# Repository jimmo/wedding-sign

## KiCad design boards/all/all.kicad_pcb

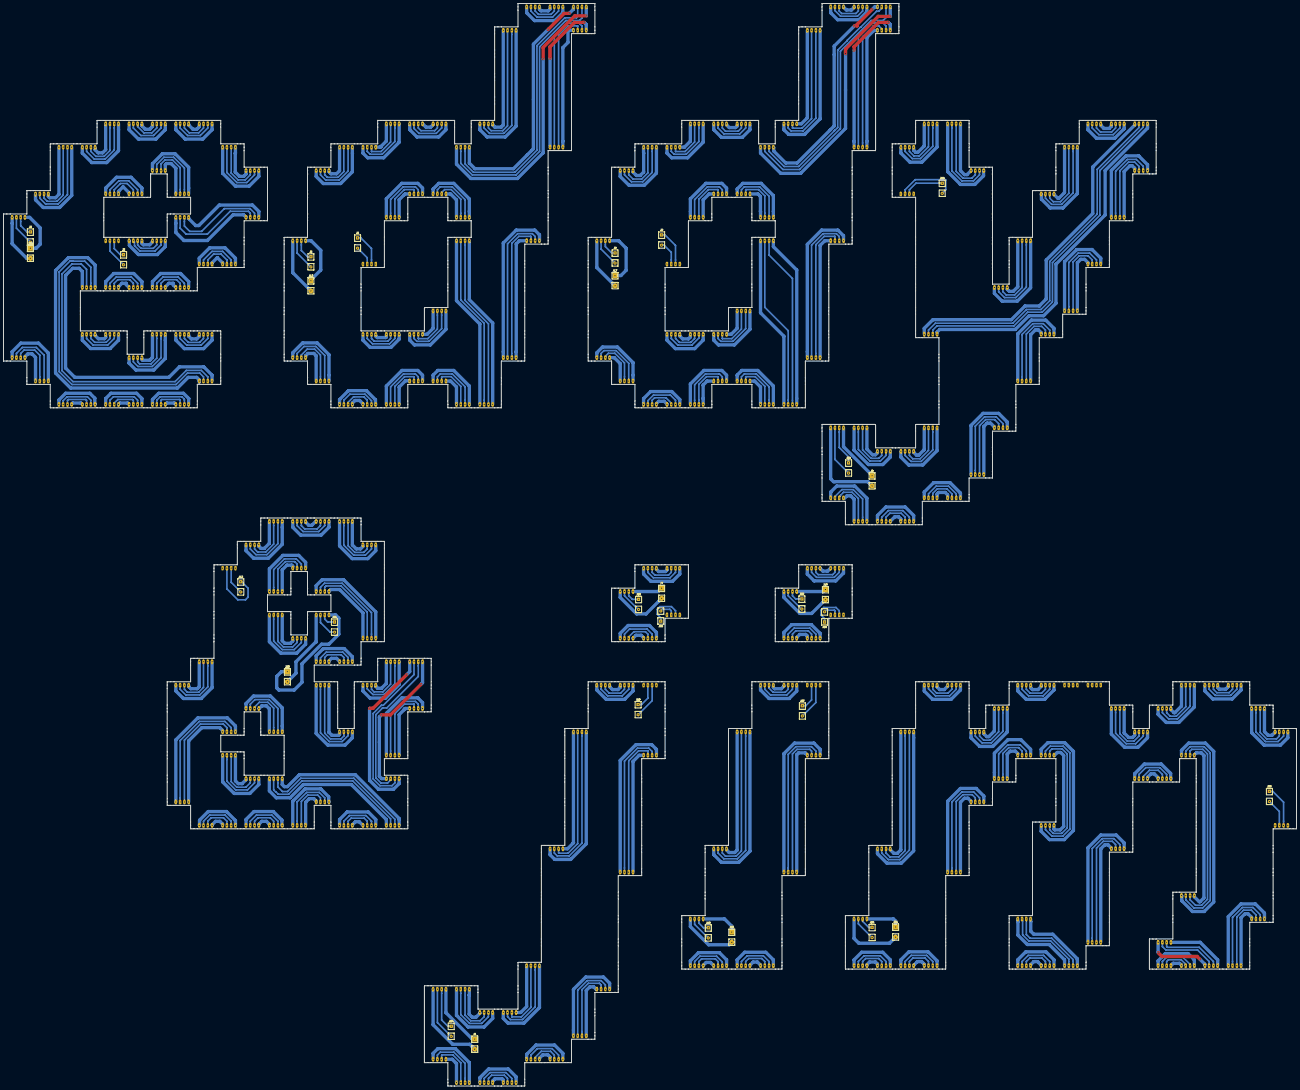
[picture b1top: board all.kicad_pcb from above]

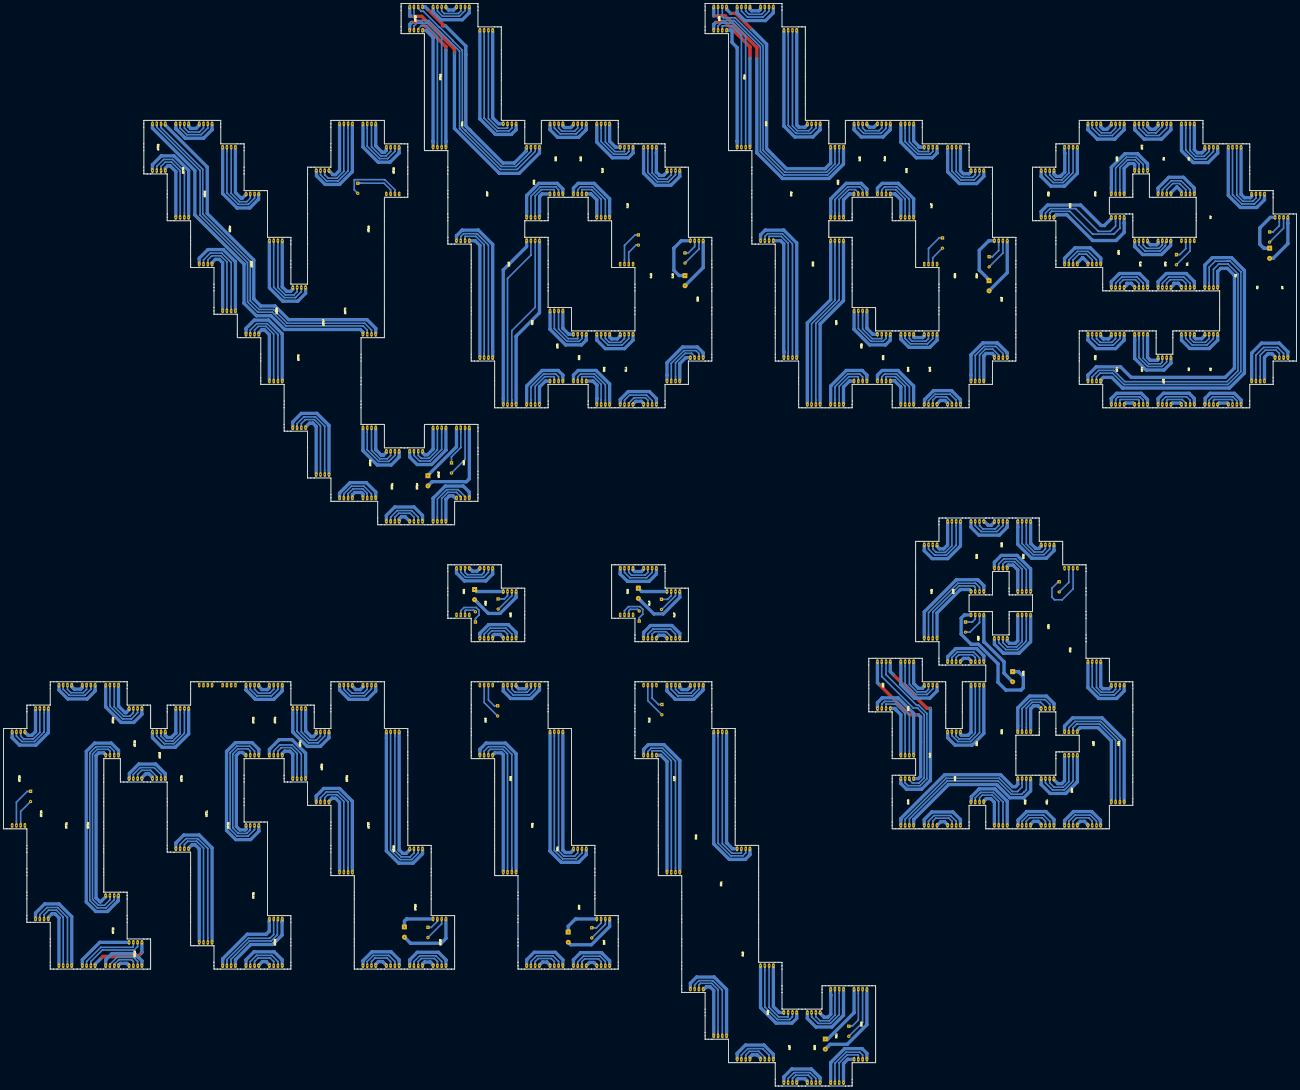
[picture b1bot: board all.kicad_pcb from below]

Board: 2 copper layers, 767.9 x 642.9 mm, 169 parts (139 on the bottom side), 558 nets.

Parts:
J1, J4, J7, J10, J13, J15, J17, J21, J23, J25: CONN_01X02; Power_Connector
J2, J3, J5, J6, J8, J9, J11, J12, J14, J16, J18, J19, J20, J22, J24, J26, J27, J28, J29, J30: CONN_01X02; Sign_Connector
U1, U4, U19, U39, U44, U64, U100, U116, U118, U121, U123, U126, U129: APA102C_x6; APA102C_72m_x6
U2, U33, U72, U93, U113: APA102C_x8; APA102C_72m_x8
U3, U38, U73, U127: APA102C_x11; APA102C_72m_x11
U5, U6, U8, U9, U14, U15, U16, U17, U24, U28, U35, U42, U46, U49, U52, U53, U54, U55, U59, U61, U74, U75, U77, U80, U82, U85, U86, U88, U95, U96, U98, U104, U107, U110, U115, U117, U119, U122, U132, U134, U135: APA102C_x3; APA102C_72m_x3
U7, U10, U11, U12, U13, U20, U25, U27, U30, U32, U36, U48, U50, U51, U71, U78, U81, U83, U92, U99, U102, U106, U120, U130, U131: APA102C_x2; APA102C_72m_x2
U18, U22, U29, U31, U37, U41, U68, U76, U84, U105: APA102C_x5; APA102C_72m_x5
U21, U23, U26, U56, U89, U124: APA102C_x7; APA102C_72m_x7
U34, U65, U70, U109, U138: APA102C_x9; APA102C_72m_x9
U40, U43, U45, U47, U57, U63, U79, U101, U128, U139: APA102C_x4; APA102C_72m_x4
U58, U90, U91, U111, U125, U136, U137: APA102C_x12; APA102C_72m_x12
U60, U94: APA102C_x14; APA102C_72m_x14
U62, U87, U97, U108: APA102C_x10; APA102C_72m_x10
U66, U103, U133: APA102C_x1; APA102C_72m_x1
U67, U69, U114: APA102C_x13; APA102C_72m_x13
U112: APA102C_x16; APA102C_72m_x16

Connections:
+5V: J1.2, J4.2, J7.2, J10.2, J13.2, J15.2, J17.2, J21.2, J23.2, J25.2, U1.4, U31.4, U36.4, U54.4, U68.4, U71.4, U81.4, U92.4, U98.4, U102.4
GND: J1.1, J4.1, J7.1, J10.1, J13.1, J15.1, J17.1, J21.1, J23.1, J25.1, U1.1, U31.1, U36.1, U54.1, U68.1, U71.1, U81.1, U92.1, U98.1, U102.1
unnamed: J2.1, U1.2
unnamed: J2.2, U1.3
unnamed: J3.1, U7.7
unnamed: J3.2, U7.6
unnamed: J5.1, U31.2
unnamed: J5.2, U31.3
unnamed: J6.1, U41.6
unnamed: J6.2, U41.7
unnamed: J8.1, U68.2
unnamed: J8.2, U68.3
unnamed: J9.1, U76.6
unnamed: J9.2, U76.7
unnamed: J11.1, U36.2
unnamed: J11.2, U36.3
unnamed: J12.1, U23.6
unnamed: J12.2, U23.7
unnamed: J14.1, U54.2
unnamed: J14.2, U54.3
unnamed: J16.1, U71.2
unnamed: J16.2, U71.3
unnamed: J18.1, U81.2
unnamed: J18.2, U81.3
unnamed: J19.1, U75.6
unnamed: J19.2, U75.7
unnamed: J20.1, U78.6
unnamed: J20.2, U78.7
unnamed: J22.1, U92.2
unnamed: J22.2, U92.3
unnamed: J24.1, U98.2
unnamed: J24.2, U98.3
unnamed: J26.1, U102.2
unnamed: J26.2, U102.3
unnamed: J27.1, U96.6
unnamed: J27.2, U96.7
unnamed: J28.1, U99.6
unnamed: J28.2, U99.7
unnamed: J29.1, U106.6
unnamed: J29.2, U106.7
unnamed: J30.1, U139.6
unnamed: J30.2, U139.7
unnamed: U1.5, U2.1
unnamed: U1.6, U2.2
unnamed: U1.7, U2.3
unnamed: U1.8, U2.4
unnamed: U2.5, U3.1
unnamed: U2.6, U3.2
unnamed: U2.7, U3.3
unnamed: U2.8, U3.4
unnamed: U3.5, U5.1
unnamed: U3.6, U5.2
unnamed: U3.7, U5.3
unnamed: U3.8, U5.4
unnamed: U4.5, U6.1
unnamed: U4.6, U6.2
unnamed: U4.7, U6.3
unnamed: U4.8, U6.4
unnamed: U5.5, U8.1
unnamed: U5.6, U8.2
unnamed: U5.7, U8.3
unnamed: U5.8, U8.4
unnamed: U6.5, U9.1
unnamed: U6.6, U9.2
unnamed: U6.7, U9.3
unnamed: U6.8, U9.4
unnamed: U10.1, U13.5
unnamed: U10.2, U13.6
unnamed: U10.3, U13.7
unnamed: U10.4, U13.8
unnamed: U7.1, U10.5
unnamed: U7.2, U10.6
unnamed: U7.3, U10.7
unnamed: U7.4, U10.8
unnamed: U8.5, U11.1
unnamed: U8.6, U11.2
unnamed: U8.7, U11.3
unnamed: U8.8, U11.4
unnamed: U11.5, U14.1
unnamed: U11.6, U14.2
unnamed: U11.7, U14.3
unnamed: U11.8, U14.4
unnamed: U9.5, U12.1
unnamed: U9.6, U12.2
unnamed: U9.7, U12.3
unnamed: U9.8, U12.4
unnamed: U12.5, U15.1
unnamed: U12.6, U15.2
unnamed: U12.7, U15.3
unnamed: U12.8, U15.4
unnamed: U13.1, U16.5
unnamed: U13.2, U16.6
unnamed: U13.3, U16.7
unnamed: U13.4, U16.8
unnamed: U14.5, U17.1
unnamed: U14.6, U17.2
unnamed: U14.7, U17.3
unnamed: U14.8, U17.4
unnamed: U15.5, U19.1
unnamed: U15.6, U19.2
unnamed: U15.7, U19.3
unnamed: U15.8, U19.4
unnamed: U16.1, U25.5
unnamed: U16.2, U25.6
unnamed: U16.3, U25.7
unnamed: U16.4, U25.8
unnamed: U17.5, U20.1
unnamed: U17.6, U20.2
unnamed: U17.7, U20.3
unnamed: U17.8, U20.4
unnamed: U18.1, U21.5
unnamed: U18.2, U21.6
unnamed: U18.3, U21.7
unnamed: U18.4, U21.8
unnamed: U18.5, U23.1
unnamed: U18.6, U23.2
unnamed: U18.7, U23.3
unnamed: U18.8, U23.4
unnamed: U19.5, U22.1
unnamed: U19.6, U22.2
unnamed: U19.7, U22.3
unnamed: U19.8, U22.4
unnamed: U4.1, U20.5
unnamed: U4.2, U20.6
unnamed: U4.3, U20.7
unnamed: U4.4, U20.8
unnamed: U21.1, U24.5
unnamed: U21.2, U24.6
unnamed: U21.3, U24.7
unnamed: U21.4, U24.8
unnamed: U22.5, U25.1
unnamed: U22.6, U25.2
unnamed: U22.7, U25.3
unnamed: U22.8, U25.4
unnamed: U24.1, U27.5
unnamed: U24.2, U27.6
unnamed: U24.3, U27.7
unnamed: U24.4, U27.8
unnamed: U26.1, U28.5
unnamed: U26.2, U28.6
unnamed: U26.3, U28.7
unnamed: U26.4, U28.8
unnamed: U26.5, U29.1
unnamed: U26.6, U29.2
unnamed: U26.7, U29.3
unnamed: U26.8, U29.4
unnamed: U27.1, U30.5
unnamed: U27.2, U30.6
unnamed: U27.3, U30.7
unnamed: U27.4, U30.8
unnamed: U28.1, U32.5
unnamed: U28.2, U32.6
unnamed: U28.3, U32.7
unnamed: U28.4, U32.8
unnamed: U29.5, U33.1
unnamed: U29.6, U33.2
unnamed: U29.7, U33.3
unnamed: U29.8, U33.4
unnamed: U30.1, U48.5
unnamed: U30.2, U48.6
unnamed: U30.3, U48.7
unnamed: U30.4, U48.8
unnamed: U31.5, U34.1
unnamed: U31.6, U34.2
unnamed: U31.7, U34.3
unnamed: U31.8, U34.4
unnamed: U32.1, U35.5
unnamed: U32.2, U35.6
unnamed: U32.3, U35.7
unnamed: U32.4, U35.8
unnamed: U33.5, U37.1
unnamed: U33.6, U37.2
unnamed: U33.7, U37.3
unnamed: U33.8, U37.4
unnamed: U34.5, U38.1
unnamed: U34.6, U38.2
unnamed: U34.7, U38.3
unnamed: U34.8, U38.4
unnamed: U35.1, U43.5
unnamed: U35.2, U43.6
unnamed: U35.3, U43.7
unnamed: U35.4, U43.8
unnamed: U36.5, U39.1
unnamed: U36.6, U39.2
unnamed: U36.7, U39.3
unnamed: U36.8, U39.4
unnamed: U37.5, U40.1
unnamed: U37.6, U40.2
unnamed: U37.7, U40.3
unnamed: U37.8, U40.4
unnamed: U38.5, U42.1
unnamed: U38.6, U42.2
unnamed: U38.7, U42.3
unnamed: U38.8, U42.4
unnamed: U39.5, U43.1
unnamed: U39.6, U43.2
unnamed: U39.7, U43.3
unnamed: U39.8, U43.4
unnamed: U40.5, U44.1
unnamed: U40.6, U44.2
unnamed: U40.7, U44.3
unnamed: U40.8, U44.4
unnamed: U41.1, U45.5
unnamed: U41.2, U45.6
unnamed: U41.3, U45.7
unnamed: U41.4, U45.8
unnamed: U42.5, U46.1
unnamed: U42.6, U46.2
unnamed: U42.7, U46.3
unnamed: U42.8, U46.4
unnamed: U44.5, U47.1
unnamed: U44.6, U47.2
unnamed: U44.7, U47.3
unnamed: U44.8, U47.4
unnamed: U45.1, U49.5
unnamed: U45.2, U49.6
unnamed: U45.3, U49.7
unnamed: U45.4, U49.8
unnamed: U46.5, U50.1
unnamed: U46.6, U50.2
unnamed: U46.7, U50.3
unnamed: U46.8, U50.4
unnamed: U47.5, U51.1
unnamed: U47.6, U51.2
unnamed: U47.7, U51.3
unnamed: U47.8, U51.4
unnamed: U48.1, U51.5
unnamed: U48.2, U51.6
unnamed: U48.3, U51.7
unnamed: U48.4, U51.8
unnamed: U49.1, U52.5
unnamed: U49.2, U52.6
unnamed: U49.3, U52.7
unnamed: U49.4, U52.8
unnamed: U50.5, U53.1
unnamed: U50.6, U53.2
unnamed: U50.7, U53.3
unnamed: U50.8, U53.4
unnamed: U52.1, U55.5
unnamed: U52.2, U55.6
unnamed: U52.3, U55.7
unnamed: U52.4, U55.8
unnamed: U53.5, U56.1
unnamed: U53.6, U56.2
unnamed: U53.7, U56.3
unnamed: U53.8, U56.4
unnamed: U54.5, U57.1
unnamed: U54.6, U57.2
unnamed: U54.7, U57.3
unnamed: U54.8, U57.4
unnamed: U55.1, U66.5
unnamed: U55.2, U66.6
unnamed: U55.3, U66.7
unnamed: U55.4, U66.8
unnamed: U56.5, U58.1
unnamed: U56.6, U58.2
unnamed: U56.7, U58.3
unnamed: U56.8, U58.4
unnamed: U57.5, U59.1
unnamed: U57.6, U59.2
unnamed: U57.7, U59.3
unnamed: U57.8, U59.4
unnamed: U58.5, U60.1
unnamed: U58.6, U60.2
unnamed: U58.7, U60.3
unnamed: U58.8, U60.4
unnamed: U59.5, U61.1
unnamed: U59.6, U61.2
unnamed: U59.7, U61.3
unnamed: U59.8, U61.4
unnamed: U60.5, U62.1
unnamed: U60.6, U62.2
unnamed: U60.7, U62.3
unnamed: U60.8, U62.4
unnamed: U61.5, U63.1
unnamed: U61.6, U63.2
unnamed: U61.7, U63.3
unnamed: U61.8, U63.4
unnamed: U62.5, U64.1
unnamed: U62.6, U64.2
unnamed: U62.7, U64.3
unnamed: U62.8, U64.4
unnamed: U63.5, U65.1
unnamed: U63.6, U65.2
unnamed: U63.7, U65.3
unnamed: U63.8, U65.4
unnamed: U64.5, U66.1
unnamed: U64.6, U66.2
unnamed: U64.7, U66.3
unnamed: U64.8, U66.4
unnamed: U65.5, U67.1
unnamed: U65.6, U67.2
unnamed: U65.7, U67.3
unnamed: U65.8, U67.4
unnamed: U67.5, U69.1
unnamed: U67.6, U69.2
unnamed: U67.7, U69.3
unnamed: U67.8, U69.4
unnamed: U68.5, U70.1
unnamed: U68.6, U70.2
unnamed: U68.7, U70.3
unnamed: U68.8, U70.4
unnamed: U69.5, U72.1
unnamed: U69.6, U72.2
unnamed: U69.7, U72.3
unnamed: U69.8, U72.4
unnamed: U70.5, U73.1
unnamed: U70.6, U73.2
unnamed: U70.7, U73.3
unnamed: U70.8, U73.4
unnamed: U71.5, U74.1
unnamed: U71.6, U74.2
unnamed: U71.7, U74.3
unnamed: U71.8, U74.4
unnamed: U72.5, U75.1
unnamed: U72.6, U75.2
unnamed: U72.7, U75.3
unnamed: U72.8, U75.4
unnamed: U73.5, U77.1
unnamed: U73.6, U77.2
unnamed: U73.7, U77.3
unnamed: U73.8, U77.4
unnamed: U74.5, U78.1
unnamed: U74.6, U78.2
unnamed: U74.7, U78.3
unnamed: U74.8, U78.4
unnamed: U76.1, U79.5
unnamed: U76.2, U79.6
unnamed: U76.3, U79.7
unnamed: U76.4, U79.8
unnamed: U77.5, U80.1
unnamed: U77.6, U80.2
unnamed: U77.7, U80.3
unnamed: U77.8, U80.4
unnamed: U79.1, U82.5
unnamed: U79.2, U82.6
unnamed: U79.3, U82.7
unnamed: U79.4, U82.8
unnamed: U80.5, U83.1
unnamed: U80.6, U83.2
unnamed: U80.7, U83.3
unnamed: U80.8, U83.4
unnamed: U81.5, U84.1
unnamed: U81.6, U84.2
unnamed: U81.7, U84.3
unnamed: U81.8, U84.4
unnamed: U82.1, U85.5
unnamed: U82.2, U85.6
unnamed: U82.3, U85.7
unnamed: U82.4, U85.8
unnamed: U83.5, U86.1
unnamed: U83.6, U86.2
unnamed: U83.7, U86.3
unnamed: U83.8, U86.4
unnamed: U84.5, U87.1
unnamed: U84.6, U87.2
unnamed: U84.7, U87.3
unnamed: U84.8, U87.4
unnamed: U85.1, U88.5
unnamed: U85.2, U88.6
unnamed: U85.3, U88.7
unnamed: U85.4, U88.8
unnamed: U86.5, U89.1
unnamed: U86.6, U89.2
unnamed: U86.7, U89.3
unnamed: U86.8, U89.4
unnamed: U87.5, U90.1
unnamed: U87.6, U90.2
unnamed: U87.7, U90.3
unnamed: U87.8, U90.4
unnamed: U89.5, U91.1
unnamed: U89.6, U91.2
unnamed: U89.7, U91.3
unnamed: U89.8, U91.4
unnamed: U90.5, U93.1
unnamed: U90.6, U93.2
unnamed: U90.7, U93.3
unnamed: U90.8, U93.4
unnamed: U91.5, U94.1
unnamed: U91.6, U94.2
unnamed: U91.7, U94.3
unnamed: U91.8, U94.4
unnamed: U92.5, U95.1
unnamed: U92.6, U95.2
unnamed: U92.7, U95.3
unnamed: U92.8, U95.4
unnamed: U93.5, U96.1
unnamed: U93.6, U96.2
unnamed: U93.7, U96.3
unnamed: U93.8, U96.4
unnamed: U94.5, U97.1
unnamed: U94.6, U97.2
unnamed: U94.7, U97.3
unnamed: U94.8, U97.4
unnamed: U95.5, U99.1
unnamed: U95.6, U99.2
unnamed: U95.7, U99.3
unnamed: U95.8, U99.4
unnamed: U97.5, U100.1
unnamed: U97.6, U100.2
unnamed: U97.7, U100.3
unnamed: U97.8, U100.4
unnamed: U100.5, U103.1
unnamed: U100.6, U103.2
unnamed: U100.7, U103.3
unnamed: U100.8, U103.4
unnamed: U98.5, U101.1
unnamed: U98.6, U101.2
unnamed: U98.7, U101.3
unnamed: U98.8, U101.4
unnamed: U101.5, U104.1
unnamed: U101.6, U104.2
unnamed: U101.7, U104.3
unnamed: U101.8, U104.4
unnamed: U102.5, U105.1
unnamed: U102.6, U105.2
unnamed: U102.7, U105.3
unnamed: U102.8, U105.4
unnamed: U88.1, U103.5
unnamed: U88.2, U103.6
unnamed: U88.3, U103.7
unnamed: U88.4, U103.8
unnamed: U104.5, U107.1
unnamed: U104.6, U107.2
unnamed: U104.7, U107.3
unnamed: U104.8, U107.4
unnamed: U105.5, U108.1
unnamed: U105.6, U108.2
unnamed: U105.7, U108.3
unnamed: U105.8, U108.4
unnamed: U106.1, U109.5
unnamed: U106.2, U109.6
unnamed: U106.3, U109.7
unnamed: U106.4, U109.8
unnamed: U107.5, U110.1
unnamed: U107.6, U110.2
unnamed: U107.7, U110.3
unnamed: U107.8, U110.4
unnamed: U108.5, U111.1
unnamed: U108.6, U111.2
unnamed: U108.7, U111.3
unnamed: U108.8, U111.4
unnamed: U109.1, U130.5
unnamed: U109.2, U130.6
unnamed: U109.3, U130.7
unnamed: U109.4, U130.8
unnamed: U110.5, U112.1
unnamed: U110.6, U112.2
unnamed: U110.7, U112.3
unnamed: U110.8, U112.4
unnamed: U111.5, U113.1
unnamed: U111.6, U113.2
unnamed: U111.7, U113.3
unnamed: U111.8, U113.4
unnamed: U112.5, U114.1
unnamed: U112.6, U114.2
unnamed: U112.7, U114.3
unnamed: U112.8, U114.4
unnamed: U113.5, U115.1
unnamed: U113.6, U115.2
unnamed: U113.7, U115.3
unnamed: U113.8, U115.4
unnamed: U114.5, U116.1
unnamed: U114.6, U116.2
unnamed: U114.7, U116.3
unnamed: U114.8, U116.4
unnamed: U115.5, U117.1
unnamed: U115.6, U117.2
unnamed: U115.7, U117.3
unnamed: U115.8, U117.4
unnamed: U116.5, U118.1
unnamed: U116.6, U118.2
unnamed: U116.7, U118.3
unnamed: U116.8, U118.4
unnamed: U117.5, U119.1
unnamed: U117.6, U119.2
unnamed: U117.7, U119.3
unnamed: U117.8, U119.4
unnamed: U118.5, U121.1
unnamed: U118.6, U121.2
unnamed: U118.7, U121.3
unnamed: U118.8, U121.4
unnamed: U119.5, U122.1
unnamed: U119.6, U122.2
unnamed: U119.7, U122.3
unnamed: U119.8, U122.4
unnamed: U120.1, U123.5
unnamed: U120.2, U123.6
unnamed: U120.3, U123.7
unnamed: U120.4, U123.8
unnamed: U120.5, U125.1
unnamed: U120.6, U125.2
unnamed: U120.7, U125.3
unnamed: U120.8, U125.4
unnamed: U121.5, U124.1
unnamed: U121.6, U124.2
unnamed: U121.7, U124.3
unnamed: U121.8, U124.4
unnamed: U122.5, U123.1
unnamed: U122.6, U123.2
unnamed: U122.7, U123.3
unnamed: U122.8, U123.4
unnamed: U124.5, U126.1
unnamed: U124.6, U126.2
unnamed: U124.7, U126.3
unnamed: U124.8, U126.4
unnamed: U125.5, U127.1
unnamed: U125.6, U127.2
unnamed: U125.7, U127.3
unnamed: U125.8, U127.4
unnamed: U126.5, U128.1
unnamed: U126.6, U128.2
unnamed: U126.7, U128.3
unnamed: U126.8, U128.4
unnamed: U127.5, U129.1
unnamed: U127.6, U129.2
unnamed: U127.7, U129.3
unnamed: U127.8, U129.4
unnamed: U128.5, U130.1
unnamed: U128.6, U130.2
unnamed: U128.7, U130.3
unnamed: U128.8, U130.4
unnamed: U129.5, U131.1
unnamed: U129.6, U131.2
unnamed: U129.7, U131.3
unnamed: U129.8, U131.4
unnamed: U131.5, U132.1
unnamed: U131.6, U132.2
unnamed: U131.7, U132.3
unnamed: U131.8, U132.4
unnamed: U132.5, U134.1
unnamed: U132.6, U134.2
unnamed: U132.7, U134.3
unnamed: U132.8, U134.4
unnamed: U133.1, U135.5
unnamed: U133.2, U135.6
unnamed: U133.3, U135.7
unnamed: U133.4, U135.8
unnamed: U133.5, U136.1
unnamed: U133.6, U136.2
unnamed: U133.7, U136.3
unnamed: U133.8, U136.4
unnamed: U134.5, U135.1
unnamed: U134.6, U135.2
unnamed: U134.7, U135.3
unnamed: U134.8, U135.4
unnamed: U136.5, U137.1
unnamed: U136.6, U137.2
unnamed: U136.7, U137.3
unnamed: U136.8, U137.4
unnamed: U137.5, U138.1
unnamed: U137.6, U138.2
unnamed: U137.7, U138.3
unnamed: U137.8, U138.4
unnamed: U138.5, U139.1
unnamed: U138.6, U139.2
unnamed: U138.7, U139.3
unnamed: U138.8, U139.4

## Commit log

2017-06-25 Initial demo.
2017-06-25 hand-modify pixels.
2017-06-29 Move to demo dir
2017-06-29 Add a png->sch converter with vertical runs.
2017-06-29 Add generated schematic with nets for 'e' Start adding footprint
2017-06-29 Start auto-generating PCB layout.
2017-06-30 Fix layout of 'e'
2017-06-30 Route 'e'
2017-06-30 nets for 'i'
2017-06-30 Add cuts layer.
2017-07-04 Update edge cuts
2017-07-04 Add more demo modes
2017-07-04 Wire up some more letters.
2017-07-08 Wire all the letters!
2017-07-09 Untangle all the pcb letters and wire up both d's.
2017-07-09 finish all the tracks
2017-07-09 Layout done!
2017-07-09 Update plots
2017-07-10 Split letters into individual kicad projects.
2017-07-10 Generate gerbers for all letters. Use a single drill size.
2017-07-11 Add flatcam workflow for 'dot'
2017-09-03 Boards made! Start implementing controller.
2017-09-03 Update gitignore
2017-09-17 Update controller!
2017-09-18 Update to use much-faster memoryview.
2017-09-18 Add circle effect
2017-09-20 Add more effect
2017-09-20 Add heat mode and some minor optmizations.
2017-09-22 Version 1.0 !!
2017-10-15 Add laser cut diffuser.
